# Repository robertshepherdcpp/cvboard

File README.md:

# cvboard
my cvboard for hackclub

## why did i build it
the general description for this project:

`a simple keyboard that has 2 keys, used for copying and pasting. one key will copy (control c equivalent) and the other will paste (control v equivalent) i have chosen this project because it is relatively simple and i am new to hardware and would like something manageable to start off with! id like to build this because i find myself copying and pasting a lot for several different things and i think it would be cool to have my own copy paste keyboord, i know i can reprogram the f keys to do the same thing, but i think it would be better to have my own dedicated one haha. im exited to start building!! i had seen a similiar thing to this being done on dragons den/shark tank and i thought it would be cool to see if i could recreate it im thinking of also adding a little twisting nob that can flip what each button maps to, so can switch round which is copy and which one is paste - however i am not too sure how feasable this is.`

so in short: i saw this cool thing on shark tank (however didnt get any investors) and i thought i wanted to make it similiar, as i find the cntrl v and cntrl c keys a bit annoying and it would be good to have a little keyboard that i could use just to do it for me!

## how does it work
basically there is a case for it, and the pcb itself:
- then there are 2 keys, one for control c and one for control c
- this is then connected to the computer via a usb (that goes throught the case and goes into the pcb), which sends the signals from the button press.

**to set up the project**:
- get the case: insert the pcb
- then put the lid on (and screw in)
- then add usb and can use! (just type the buttons on the keyboard and they will work as intended!)

## design considerations
- as this was my first pcb project there were several design considerations that had to be made due to failures on my part:
- i chose to not use any key pads as in the design of the pcb i had put the seeeduino-xiao on the other side of the pcb, however i didnt put the buttons in the correct place in order to use a dxf file creator for a macropad (ai03)
- as a reuslt of this, i had to make my own lid, which just had a cut out for where the buttons where, this means it has a more "hardware" kind of look, and actually kind of fits with a look i want.
- i was planning originally to add a turning nob to switch the mappings of the keys around - however i later decided against that idea.
- i was also originally going to use raspberry pi as the MCU, however i chose to switch to using the arduino mirco, as i found programming it with the arduino
ide actually easier than using QMK (as for the scale of my project for only 2 keys, i thought this was a better choice)
- also i changed from the arduino micro to the xiao-rp2040 as the mcu

## how to use it
- i havent actually built it yet, however to use it the process should go something like this:
- first flash the firmware from your computer onto the board (e.g. using the arduino ide and install the appropriate library for the mcu)
- add the Cherry keys onto the PCB, and then add the keycaps
- assemble the case (and put on the lid)
- screw in using the bolts going through the pcb.
- then use the left key for control c (copy) and use the right key for control v (paste).
- make sure you keep the project plugged into the computer - as the usb connection is the source of power.

## some screenshots of the project:
the pcb:

3d model: (.step file)

the case:

## The Zine

(a pdf can also be found in this repository)

firmware:

## BOM
total cost: $31.99 (more details in BOM.csv in this repository)

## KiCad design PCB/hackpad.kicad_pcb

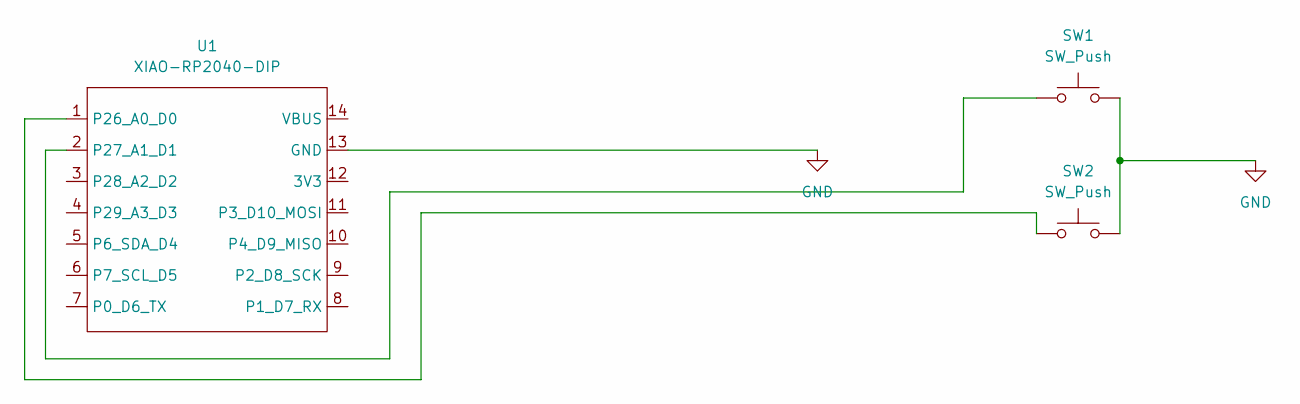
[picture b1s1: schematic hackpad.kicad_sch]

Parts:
SW1, SW2: SW_Push; SW_Cherry_MX_1.00u_PCB
U1: XIAO-RP2040-DIP

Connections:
GND: SW1.2, SW2.2, U1.13 (GND)
unnamed: SW2.1, U1.1 (P26_A0_D0)
unnamed: SW1.1, U1.2 (P27_A1_D1)

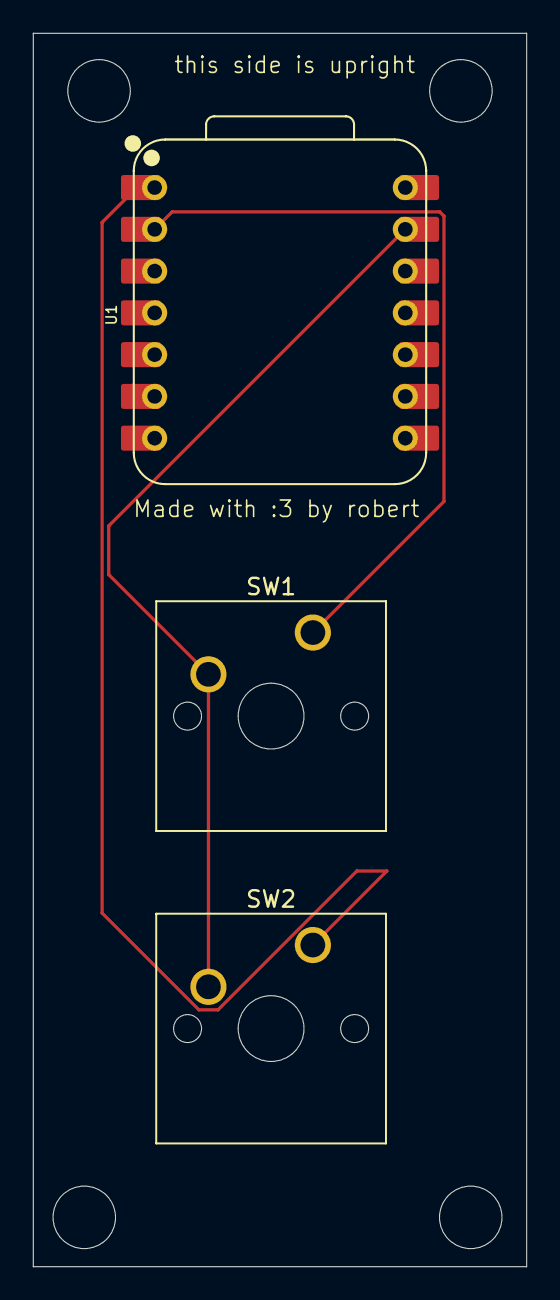
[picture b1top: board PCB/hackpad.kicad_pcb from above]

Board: 2 copper layers, 30.0 x 75.0 mm, 3 parts (0 on the bottom side), 3 nets.

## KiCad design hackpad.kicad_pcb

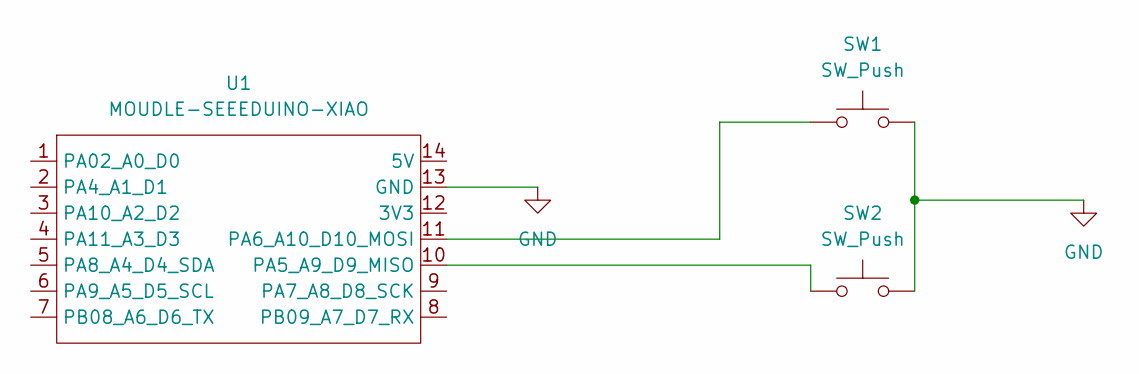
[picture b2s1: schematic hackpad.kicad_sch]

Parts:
SW1, SW2: SW_Push; SW_Cherry_MX_1.00u_PCB
U1: MOUDLE-SEEEDUINO-XIAO; XIAO-Generic-Hybrid-14P-2.54-21X17.8MM

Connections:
GND: SW1.2, SW2.2, U1.13 (GND)
unnamed: SW2.1, U1.10 (PA5_A9_D9_MISO)
unnamed: SW1.1, U1.11 (PA6_A10_D10_MOSI)

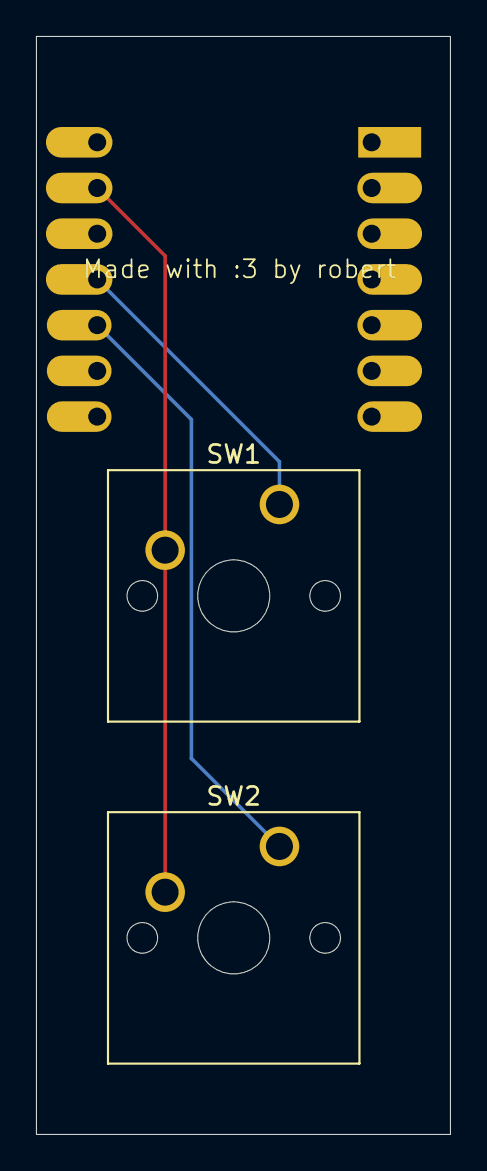
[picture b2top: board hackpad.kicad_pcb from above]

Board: 2 copper layers, 23.0 x 61.0 mm, 3 parts (1 on the bottom side), 3 nets.

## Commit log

2026-04-08 Expand README with project details and instructions
    Added detailed project description, setup instructions, design considerations, and screenshots.
2026-04-08 Revise README with project overview and functionality
    Updated project description and added details about the keyboard's functionality and components.
2026-04-10 Add additional images of the case
    Added two new images of the case to the README.
2026-04-21 Update README with new PCB images
    Added additional PCB images to the README.
2026-04-21 add pcb files
2026-04-21 Rename hackpad.kicad_pcb to PCB/hackpad.kicad_pcb
2026-04-21 Rename hackpad.kicad_prl to PCB/hackpad.kicad_prl
2026-04-21 Rename hackpad.kicad_pro to PCB/hackpad.kicad_pro
2026-04-21 Rename hackpad.kicad_sch to PCB/hackpad.kicad_sch
2026-04-21 Rename hackpad.step to PCB/hackpad.step
2026-04-21 Rename hackpad_case.f3z to CAD/hackpad_case.f3z
2026-04-21 Update README with new project screenshots
    Added additional screenshots of the project, including the PCB and case images.
2026-04-21 add the firmware
2026-04-21 Rename sketch_apr21a_copy_20260421140711.ino to FIRMWARE/sketch_apr21a_copy_20260421140711.ino
2026-04-21 Fix header format in BOM.csv
2026-04-21 Rename hackpad_4.f3d to CAD/hackpad.f3d
2026-04-21 Rename Untitled (3).pdf to ZINE/Untitled (3).pdf
2026-04-21 Rename Untitled (3).pdf to cvboard-zine.pdf
2026-04-24 Update BOM.csv
    add the updated prices (not the ones that require the new user discount, these only apply to one anyway)
2026-04-24 Add total cost information to README
2026-04-24 Add image to README with total cost information
2026-04-29 Add image to the Zine section in README
    Added a new image to the Zine section of the README.
2026-04-29 Rename Untitled (2).png to zinev2.png
2026-04-29 Add exploded view image to README
    Added an image for the exploded view section in the README.
2026-05-01 Zine Final
2026-05-01 Change button pin definitions and input modes
2026-05-01 Revise project screenshots and BOM section
    Updated images and removed BOM details.
2026-05-01 Update README with setup instructions and button details
    Clarified project setup instructions and added details on button functionality.
2026-06-01 add the proper links to the bom instead of ali short ones
2026-06-01 add arduino micro cad file
2026-06-01 Rename ARDUINO MICRO.step to CAD/ARDUINO MICRO.step
2026-06-01 add additional step files
2026-06-01 add updated pcb files
2026-06-02 Rename Untitled (11).pdf to FINAL.pdf
2026-06-02 FINAL FINAL
2026-06-02 Rename Untitled (12).pdf to Zine/zine.pdf
2026-06-08 add the total cost row
2026-06-08 add the updated bom to the readme
2026-06-08 Update README with more project screenshots
    Added additional images to showcase the project.
2026-06-08 add the updated zine.
2026-06-08 Rename Untitled (15).pdf to zine.pdf
2026-06-08 add the updated gerber files
2026-06-08 addint the new pcb files.
2026-06-08 add the actual mcu used.
2026-06-08 pcb step file.
2026-06-08 Rename hackpad.step to hackpad_pcb.step
2026-06-08 add the case - full model
2026-06-09 add the new zine.
2026-06-09 Rename Untitled (17).pdf to zinepdf
2026-06-09 Rename zinepdf to zine.pdf
2026-06-09 add the fusion file.
2026-06-09 Revise usage instructions in README
    Updated instructions for flashing firmware and assembly process.
